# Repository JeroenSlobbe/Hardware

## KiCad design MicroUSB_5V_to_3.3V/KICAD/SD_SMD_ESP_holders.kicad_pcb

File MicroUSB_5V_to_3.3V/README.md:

# MicroUSB-B 5V input to 3.3V output
As part of learning electronics, i'm working on a custom PCB. This custom PCB decomposes an ESP32 DevBoard, reorders it and adds functionality. For this decomposition, I decided to isolate the power supply first. As such, this custom PCB obtains the 5V input from a microUSB-B, and uses the AMS1117 Low-Dropout-Regulator (LDO) to get to a stable 3.3V. The PCB implements the original schematic from [theorycircuit](https://theorycircuit.com/power-circuits/voltage-regulator-circuit-5v-to-3-3v/):

## Shoppinglist for the components
Components to buy:
| ID | Item | URL | Price (EUR) |
|-----|-----------|-----------|-----------|
|     1| Micro USB | https://www.distrelec.nl/nl/usb-connectoren-aansluiting-micro-usb-rechte-hoek-posities-wuerth-elektronik-629105150521/p/30009163 | 1.81 |    
|     2| AMS 1117 LDO | https://www.amazon.nl/dp/B019JV856Q?psc=1&ref=ppx_yo2ov_dt_b_product_details | 0.599 |
|     3| 220 &Omega; resistor, 10&mu;f capacitator, led | https://www.amazon.nl/gp/product/B08QGD9G7C | 0.017 |

# Design decissions & Improvements

- [x] Decission: to use a [via](https://en.wikipedia.org/wiki/Via_(electronics)) to connect the AMS1117 3.3V output towards the pin. Although it would be possible to wire it, such that no wires overlap, I wanted to use a via for educational purposes;
- [ ] Improvement: redo wiring, so that the ground and vcc input don't need to cross within the microUSB footprint;
- [x] Improvement: add VCC, GND and PWR_FLAG symbols, as well as the NO_CONNECT flag for pins of the USB not being used;
- [ ] Improvement: calculate precise track size according to the IPC-2152 standard / as described [in this article](https://www.studiopieters.nl/track/).

The end result:

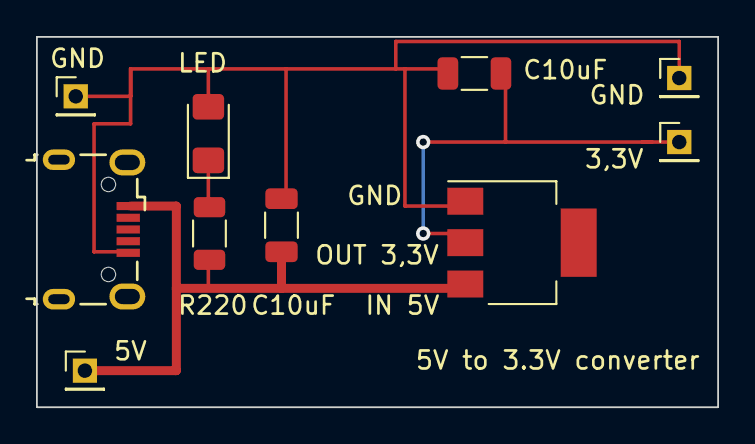
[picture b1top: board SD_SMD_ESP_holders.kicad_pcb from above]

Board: 2 copper layers, 37.8 x 20.6 mm, 10 parts (0 on the bottom side), 4 nets, no tracks yet.

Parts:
C1, C2: C_Small; C_1206_3216Metric
D1: LED; LED_1206_3216Metric_Pad1.42x1.75mm_HandSolder
J2: USB_B_Micro; USB_Micro-B_Wuerth_629105150521
J3, J4, J5, J5#2: Conn_01x01_Pin; PinHeader_1x01_P2.00mm_Vertical
R1: R_Small; R_1206_3216Metric
U2: AP1117-33; SOT-223-3_TabPin2

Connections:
unnamed: D1.2 (A), R1.2
unnamed: C1.2, C2.2, D1.1 (K), J5#2.1, U2.1 (GND)
unnamed: C1.1, J2.1 (VBUS), J3.1, R1.1, U2.3 (VI)
unnamed: C2.1, U2.2 (VO)

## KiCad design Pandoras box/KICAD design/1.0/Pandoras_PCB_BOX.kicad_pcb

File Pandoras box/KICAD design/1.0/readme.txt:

The PCB is designed using KICAD 7.0.6 which can be downloaded via: https://www.kicad.org/download/

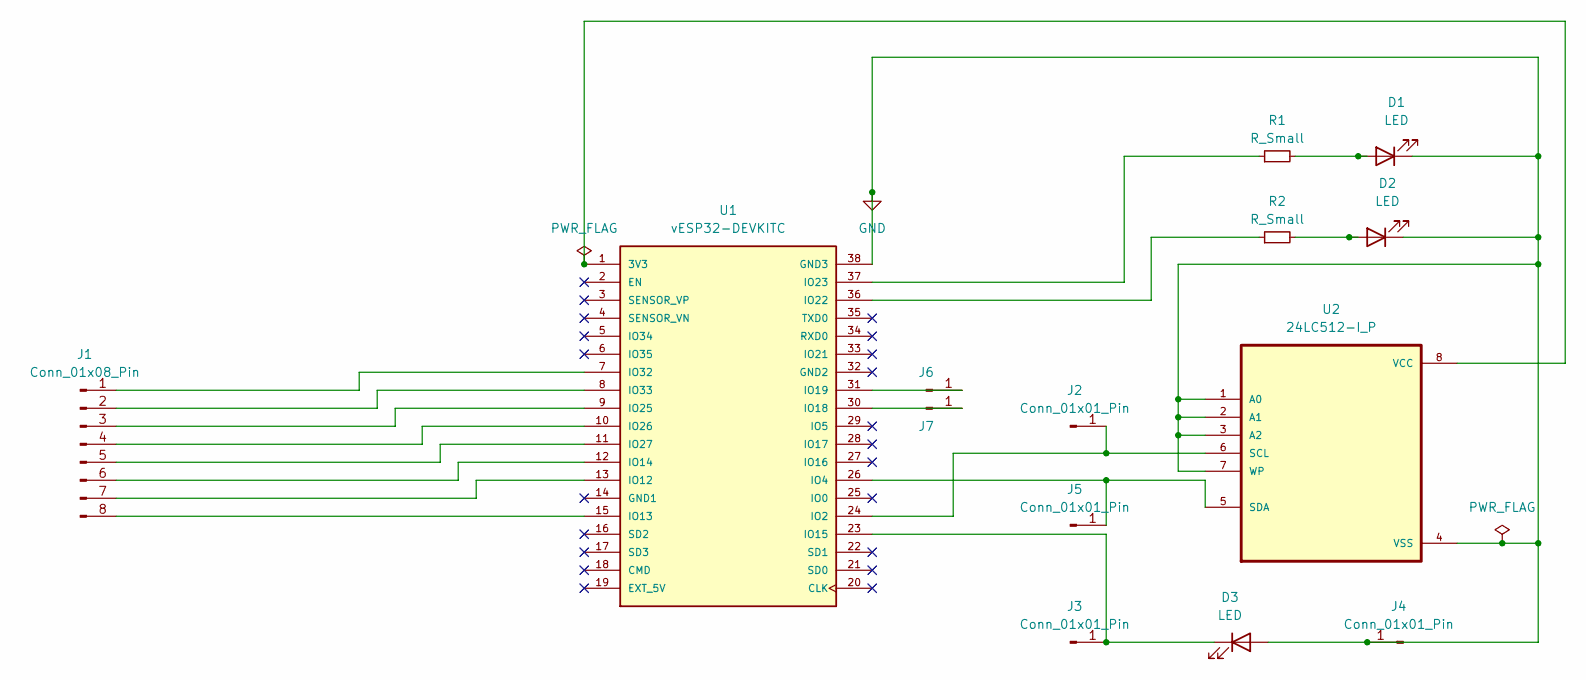
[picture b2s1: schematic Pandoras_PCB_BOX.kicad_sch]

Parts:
D1, D2, D3: LED; LED_D3.0mm_Clear
J1: Conn_01x08_Pin; PinHeader_1x08_P2.54mm_Horizontal
J2, J3, J4, J5, J6, J7: Conn_01x01_Pin; PinHeader_1x01_P2.00mm_Vertical
R1, R2: R_Small; R_Axial_DIN0204_L3.6mm_D1.6mm_P5.08mm_Horizontal
U1: vESP32-DEVKITC; MODULE_ESP32-DEVKITC; PARTREV N/A
U2: 24LC512-I_P; DIP787W46P254L927H533Q8

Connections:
GND: D1.1 (K), D2.1 (K), D3.2 (A), J4.1, U1.38 (GND3), U2.1 (A0), U2.2 (A1), U2.3 (A2), U2.4 (VSS), U2.7 (WP)
unnamed: D1.2 (A), R1.2
unnamed: D2.2 (A), R2.2
unnamed: D3.1 (K), J3.1, U1.23 (IO15)
unnamed: J1.1, U1.7 (IO32)
unnamed: J1.2, U1.8 (IO33)
unnamed: J1.3, U1.9 (IO25)
unnamed: J1.4, U1.10 (IO26)
unnamed: J1.5, U1.11 (IO27)
unnamed: J1.6, U1.12 (IO14)
unnamed: J1.7, U1.13 (IO12)
unnamed: J1.8, U1.15 (IO13)
unnamed: J2.1, U1.24 (IO2), U2.6 (SCL)
unnamed: J5.1, U1.26 (IO4), U2.5 (SDA)
unnamed: J6.1, U1.31 (IO19)
unnamed: J7.1, U1.30 (IO18)
unnamed: U1.1 (3V3), U2.8 (VCC)
unnamed: R2.1, U1.36 (IO22)
unnamed: R1.1, U1.37 (IO23)

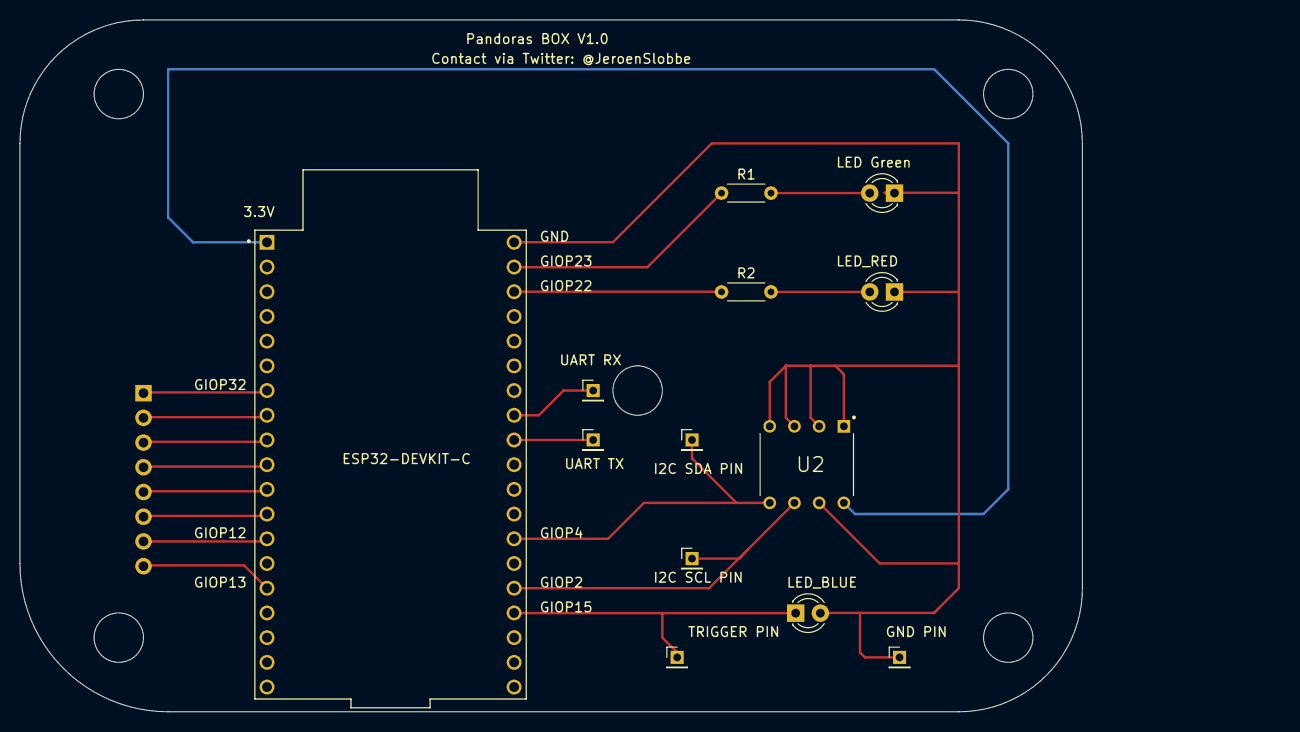
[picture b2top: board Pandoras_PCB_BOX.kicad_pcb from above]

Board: 2 copper layers, 109.2 x 71.1 mm, 14 parts (1 on the bottom side), 19 nets.

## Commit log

2023-11-25 Create Protocols
2023-12-06 Create ReadwriteEEPROM
2023-12-07 Rename ReadwriteEEPROM to ReadwriteEEPROM.ino
2024-01-04 Rename readme.txt to readme.md
2024-01-05 readme.txt
2024-01-07 Update Pandorasbox.ino
    Added UART support for pins 18/19
2024-01-07 Update Pandorasbox.ino
    Freeing up PINs 18/19 by using GPIO 3/1 (Default RX/TX) pins for UART comm. PINs can be removed after next PCB update, keeping them for now
2024-01-07 Update Pandorasbox.ino
    Adding WiFi Hotspot
2024-06-10 Rename README to README.md
2024-06-10 Create a
